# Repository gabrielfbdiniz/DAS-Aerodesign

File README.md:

# DAS V2 — Sistema de Aquisição de Dados de Voo
**Equipe de AeroDesign — Temporada 2025/2026**  
*Placa de Aviônica Integrada, Telemetria e Posicionamento GNSS RTK Centimétrico*

[-red.svg)](https://www.st.com)

---

## 1. Visão Geral do Projeto

O **DAS V2 (Data Acquisition System V2)** é a nova geração da aviônica de bordo da aeronave da equipe de AeroDesign. 

Projetada a partir do zero para superar as limitações térmicas e de estabilidade da versão anterior (V1), a placa unifica em um único PCB de 4 camadas:
* Processamento matemático de alto desempenho com FPU de ponto flutuante em hardware;
* Posicionamento geodésico centimétrico ($1\text{ cm} - 2\text{ cm}$) via RTK/PPK multibanda;
* Fusão de dados inerciais de 9 graus de liberdade (IMU);
* Telemetria do trem de força elétrico via barramento CAN ligado ao VESC;
* Armazenamento em alta velocidade em cartão MicroSD via SPI com DMA;
* Alimentação chaveada de alta eficiência suportando baterias LiPo 2S a 4S ($7.4\text{ V} - 16.8\text{ V}$) sem aquecimento.

---

## 2. Renders 3D da Placa (PCB 4 Camadas — 50 × 90 mm)

| Vista Superior (Top — `F.Cu`) | Vista Inferior (Bottom — `B.Cu`) |
| :---: | :---: |
|  |  |

---

## 3. Especificações Técnicas

| Subsistema | Componente / Chip | Características Principais |
| :--- | :--- | :--- |
| **Dimensões / Stackup** | **PCB 4 Camadas** ($50 \times 90\text{ mm}$) | Empilhamento `F.Cu` / `In1.Cu` (GND) / `In2.Cu` (PWR) / `B.Cu`, 128 componentes (passivos 0603 *HandSolder*). |
| **Microcontrolador** | **STM32G431CBT6** (LQFP-48) | ARM Cortex-M4F @ 170 MHz com FPU, 128 kB Flash, 32 kB SRAM, FDCAN nativo, cristal HSE 16 MHz. |
| **GNSS RTK** | **u-blox ZED-F9P-02B** | Receptor multibanda L1/L2 (GPS, GLONASS, Galileo, BeiDou), RTK centimétrico e logs brutos para PPK. |
| **Linha RF GNSS** | Conector SMA Borda 50 $\Omega$ (`J8`) | Bias-T ativo onboard (`VCC_RF`), filtro choke 47 nH e diodo TVS de ultrabaixa capacitância **PESD5V0X1BA**. |
| **IMU (9-DOF)** | **Bosch BNO055** | Acelerômetro, Giroscópio e Magnetômetro com fusão em quatérnions via I2C1 (`0x28`). |
| **Barômetro** | **TE MS5611-01BA** | Sensor barométrico de alta resolução (24 bits) no barramento I2C1 (`0x77`). |
| **Multiplexador I2C** | **TI PCA9548APW** | Multiplexador I2C de 8 canais no barramento I2C3 (`0x70`), com 4 portas JST-PH dedicadas (`J4`, `J12`–`J14`) para Pitot e expansões. |
| **Telemetria VESC / CAN** | **SN65HVD230** + TVS **NUP2105L** | Transceptor CAN 3.3V com terminação split $120\,\Omega$ configurável (`JP1`/`JP2`) e dois conectores JST-PH (`J7` VESC e `J10` Expansão). |
| **Armazenamento** | Slot MicroSD (`J5`, Push-Push) | Interface SPI1 de alta velocidade com DMA (>1.5 MB/s de escrita sustentada), montado na face inferior. |
| **Telemetria RF & Pixhawk** | Conectores JST-PH 2.0 mm (`J6`, `J11`) | UART2 dedicada para rádio modem de longo alcance (`J6`) e UART3 para interface Pixhawk / MAVLink (`J11`). |
| **Interface USB** | Conector USB-C 16 Pinos (`J2`) | Proteção ESD dedicada **USBLC6-2SC6**, resistores CC de $5.1\text{ k}\Omega$ e proteção de sobretensão (`3.3 V`) para `V_USB` do GNSS. |
| **Alimentação** | **TPS563200** + **AP2112K-3.3** | Buck 5.0V @ 2A (eficiência $>90\%$) + LDO 3.3V de baixo ruído, entrada XT30 (`J1`) 7.4V–16.8V (LiPo 2S–4S) com proteção P-MOSFET. |

---

## 4. Arquitetura Estrutural do Repositório

O repositório adota estrutura de **monorepo** separando hardware (KiCad 10), firmware (`STM32G431CBT6`) e documentação:

```
DAS_V2/
├── .gitignore                          # Regras de exclusão de temporários, backups e builds
├── README.md                           # Documentação principal do projeto
├── docs/                               # Documentação Técnica Aprofundada
│   ├── images/                         # Renders 3D da PCB (Top, Bottom e Isométrico)
│   │   ├── das_v2_iso.png
│   │   ├── das_v2_top.png
│   │   └── das_v2_bottom.png
│   ├── GUIA_OPERACAO_RTK_PPK.md        # Guia Completo: Operação RTK, Base de Solo, NTRIP e PPK
│   ├── RELATORIO_AUDITORIA_ESQUEMATICO_DAS_V2.md
│   └── PLANO_DE_ACAO.md                # Diagnóstico forense da V1 e diretrizes do redesenho V2
├── hardware/                           # Projeto KiCad 10 (Esquemático, PCB e Bibliotecas)
│   ├── DAS_V2.kicad_pro                # Arquivo principal do projeto KiCad 10
│   ├── DAS_V2.kicad_sch                # Folha Raiz (Top-Level) com barramentos interfolhas
│   ├── 01_Power_Supply.kicad_sch       # Módulo 1: Entrada XT30, Proteção P-FET, Buck 5V e LDO 3.3V
│   ├── 02_MCU_Core.kicad_sch           # Módulo 2: STM32G431, USB-C, SWD, HSE 16MHz, Reset & Status
│   ├── 03_Sensors.kicad_sch            # Módulo 3: IMU BNO055, Barômetro MS5611 e Mux I2C3 PCA9548APW
│   ├── 04_GNSS_RTK.kicad_sch           # Módulo 4: u-blox ZED-F9P, Bias-T, Linha RF 50R e Porta RTCM
│   ├── 05_Storage_Telemetry.kicad_sch  # Módulo 5: MicroSD, CAN (VESC + Expansão), RF e Pixhawk
│   ├── DAS_V2.kicad_pcb                # Layout da Placa de Circuito Impresso (Stackup 4 camadas)
│   ├── fp-lib-table                    # Tabela de bibliotecas de footprints locais
│   ├── sym-lib-table                   # Tabela de bibliotecas de símbolos locais
│   └── DAS_V2.pretty/                  # Diretório de footprints customizados (Logo AeroDesign)
└── firmware/                           # Firmware embarcado STM32G431CBT6
    └── README.md                       # Mapeamento de periféricos e instruções de firmware
```

---

## 5. Documentação Técnica em Destaque

* 🛰️ **[Guia de Operação GNSS RTK & PPK](docs/GUIA_OPERACAO_RTK_PPK.md):**
  Explica o funcionamento do ZED-F9P, por que o receptor sozinho no avião não atinge precisão centimétrica sem base, como **reaproveitar uma segunda placa DAS V2 idêntica como Estação de Solo em tripé**, como usar a rede gratuita NTRIP/IBGE (RBMC) e o passo a passo de pós-processamento com o **RTKLIB** (PPK).
* 🔍 **[Relatório de Auditoria Elétrica do Esquemático](docs/RELATORIO_AUDITORIA_ESQUEMATICO_DAS_V2.md):**
  Auditoria pino a pino de todos os CIs, apontando as correções críticas de hardware (Zener do P-MOSFET, estabilidade do LDO com cerâmica, bootloader do STM32 vs. CAN RX e capacitância do TVS de RF).
* 📋 **[Plano de Ação e Diagnóstico da V1](docs/PLANO_DE_ACAO.md):**
  Histórico forense das falhas da versão anterior e justificativas de engenharia para cada escolha de arquitetura da V2.

---

## 6. Como Abrir e Compilar o Projeto

1. Certifique-se de ter o **KiCad 10.0** ou superior instalado.
2. Clone o repositório:
   ```bash
   git clone <URL_DO_REPOSITORIO>
   cd "DAS V2"
   ```
3. Abra o arquivo de projeto:
   * Abra o KiCad e selecione `hardware/DAS_V2.kicad_pro`.
   * Clique em `Esquemático (Eeschema)` para visualizar as folhas hierárquicas.
   * Clique em `Placa (Pcbnew)` para visualizar o layout 2D/3D.

---

## 7. Padronização Mecânica e Conectores

Todos os chicotes externos da aeronave foram padronizados para garantir segurança contra vibração, leveza e facilidade de manutenção em campo:

| Conector | Função | Pinos | Padrão |
| :--- | :--- | :---: | :--- |
| **J1** | Entrada de Bateria Principal | 2 | **XT30** Vertical (`AMASS XT30UPB-M`) |
| **J2** | Interface de Programação / Dados | 16 | **USB-C** 2.0 (UFP) |
| **J3** | Debug / Gravação Firmware | 5 | SWD Header 2.54 mm (3.3V, SWDIO, SWCLK, GND, NRST) |
| **J4, J12, J13, J14** | Expansão I2C Multiplexada (Pitot / Sensores) | 4 | **JST-PH 2.0 mm** Vertical (Canais `0..3` do `PCA9548APW`) |
| **J5** | Armazenamento Local | 8+ | Slot **MicroSD** Push-Push (`Hirose DM3AT`, face inferior) |
| **J6** | Telemetria RF de Longo Alcance | 4 | **JST-PH 2.0 mm** Vertical (5.0V, GND, TX, RX — `USART2`) |
| **J7** | Telemetria VESC do Motor | 4 | **JST-PH 2.0 mm** Vertical (NC, CAN_H, CAN_L, GND) |
| **J8** | Antena GNSS Multibanda | Coaxial | **SMA Fêmea** Borda (`Edge-Mount`) 50 $\Omega$ |
| **J9** | Entrada de Correção RTCM | 4 | **JST-PH 2.0 mm** Vertical (3.3V, TX, RX, GND — `UART2` ZED-F9P) |
| **J10** | Expansão Barramento CAN | 4 | **JST-PH 2.0 mm** Vertical (CAN_H, CAN_L, GND) |
| **J11** | Interface Pixhawk / MAVLink | 4 | **JST-PH 2.0 mm** Vertical (`USART3` TX, RX, GND) |

---
*Desenvolvido com excelência técnica pela Equipe AeroDesign.*

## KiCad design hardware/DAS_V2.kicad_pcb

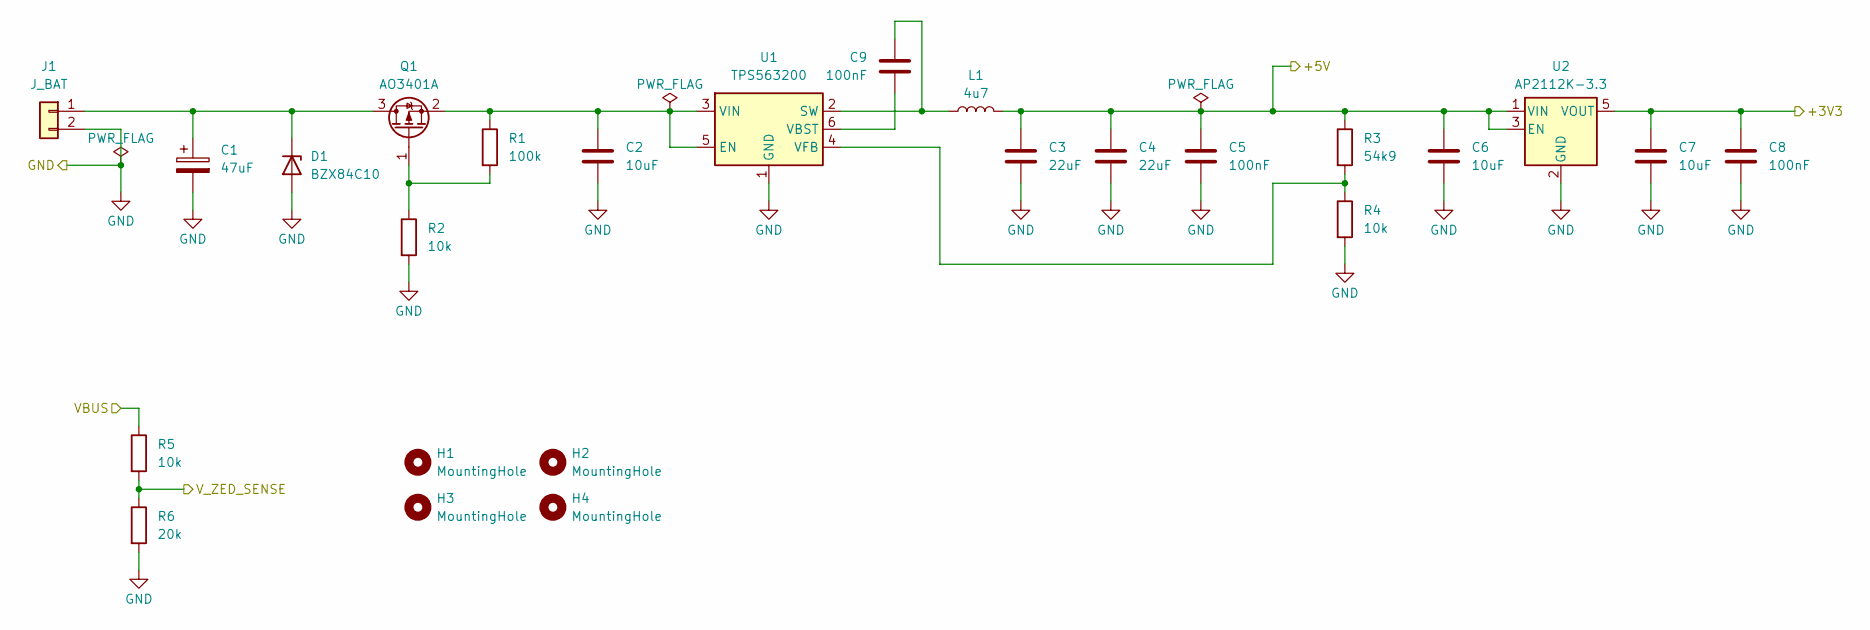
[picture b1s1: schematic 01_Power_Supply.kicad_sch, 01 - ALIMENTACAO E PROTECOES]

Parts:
C1: 47uF; CP_EIA-7343-31_Kemet-D_HandSolder
C2, C6, C7: 10uF; C_0805_2012Metric_Pad1.18x1.45mm_HandSolder
C3, C4: 22uF; C_1206_3216Metric_Pad1.33x1.80mm_HandSolder
C5, C8, C9: 100nF; C_0603_1608Metric_Pad1.08x0.95mm_HandSolder
D1: BZX84C10; SOT-23
H1, H2, H3, H4: MountingHole; MountingHole_3.2mm_M3
J1: J_BAT; AMASS_XT30UPB-M_1x02_P5.0mm_Vertical
L1: 4u7; L_APV_APH0630
Q1: AO3401A; SOT-23
R1: 100k; R_0603_1608Metric_Pad0.98x0.95mm_HandSolder
R2, R4, R5: 10k; R_0603_1608Metric_Pad0.98x0.95mm_HandSolder
R3: 54k9; R_0603_1608Metric_Pad0.98x0.95mm_HandSolder
R6: 20k; R_0603_1608Metric_Pad0.98x0.95mm_HandSolder
U1: TPS563200; SOT-23-6
U2: AP2112K-3.3; SOT-23-5

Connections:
/01_Alimentacao/+3V3: C7.1, C8.1, U2.5 (VOUT); also elsewhere on the board
/01_Alimentacao/+5V: C3.1, C4.1, C5.1, C6.1, L1.2, R3.1, U2.1 (VIN), U2.3 (EN); also elsewhere on the board
/01_Alimentacao/VBUS: R5.1; also elsewhere on the board
/01_Alimentacao/V_ZED_SENSE: R5.2, R6.1; also elsewhere on the board
GND: C1.2, C2.2, C3.2, C4.2, C5.2, C6.2, C7.2, C8.2, D1.1 (A), J1.2, R2.2, R4.2, R6.2, U1.1 (GND), U2.2 (GND); also elsewhere on the board
unnamed: C1.1, D1.3 (K), J1.1, Q1.3 (D)
unnamed: Q1.1 (G), R1.2, R2.1
unnamed: C2.1, Q1.2 (S), R1.1, U1.3 (VIN), U1.5 (EN)
unnamed: C9.1, L1.1, U1.2 (SW)
unnamed: C9.2, U1.6 (VBST)
unnamed: R3.2, R4.1, U1.4 (VFB)

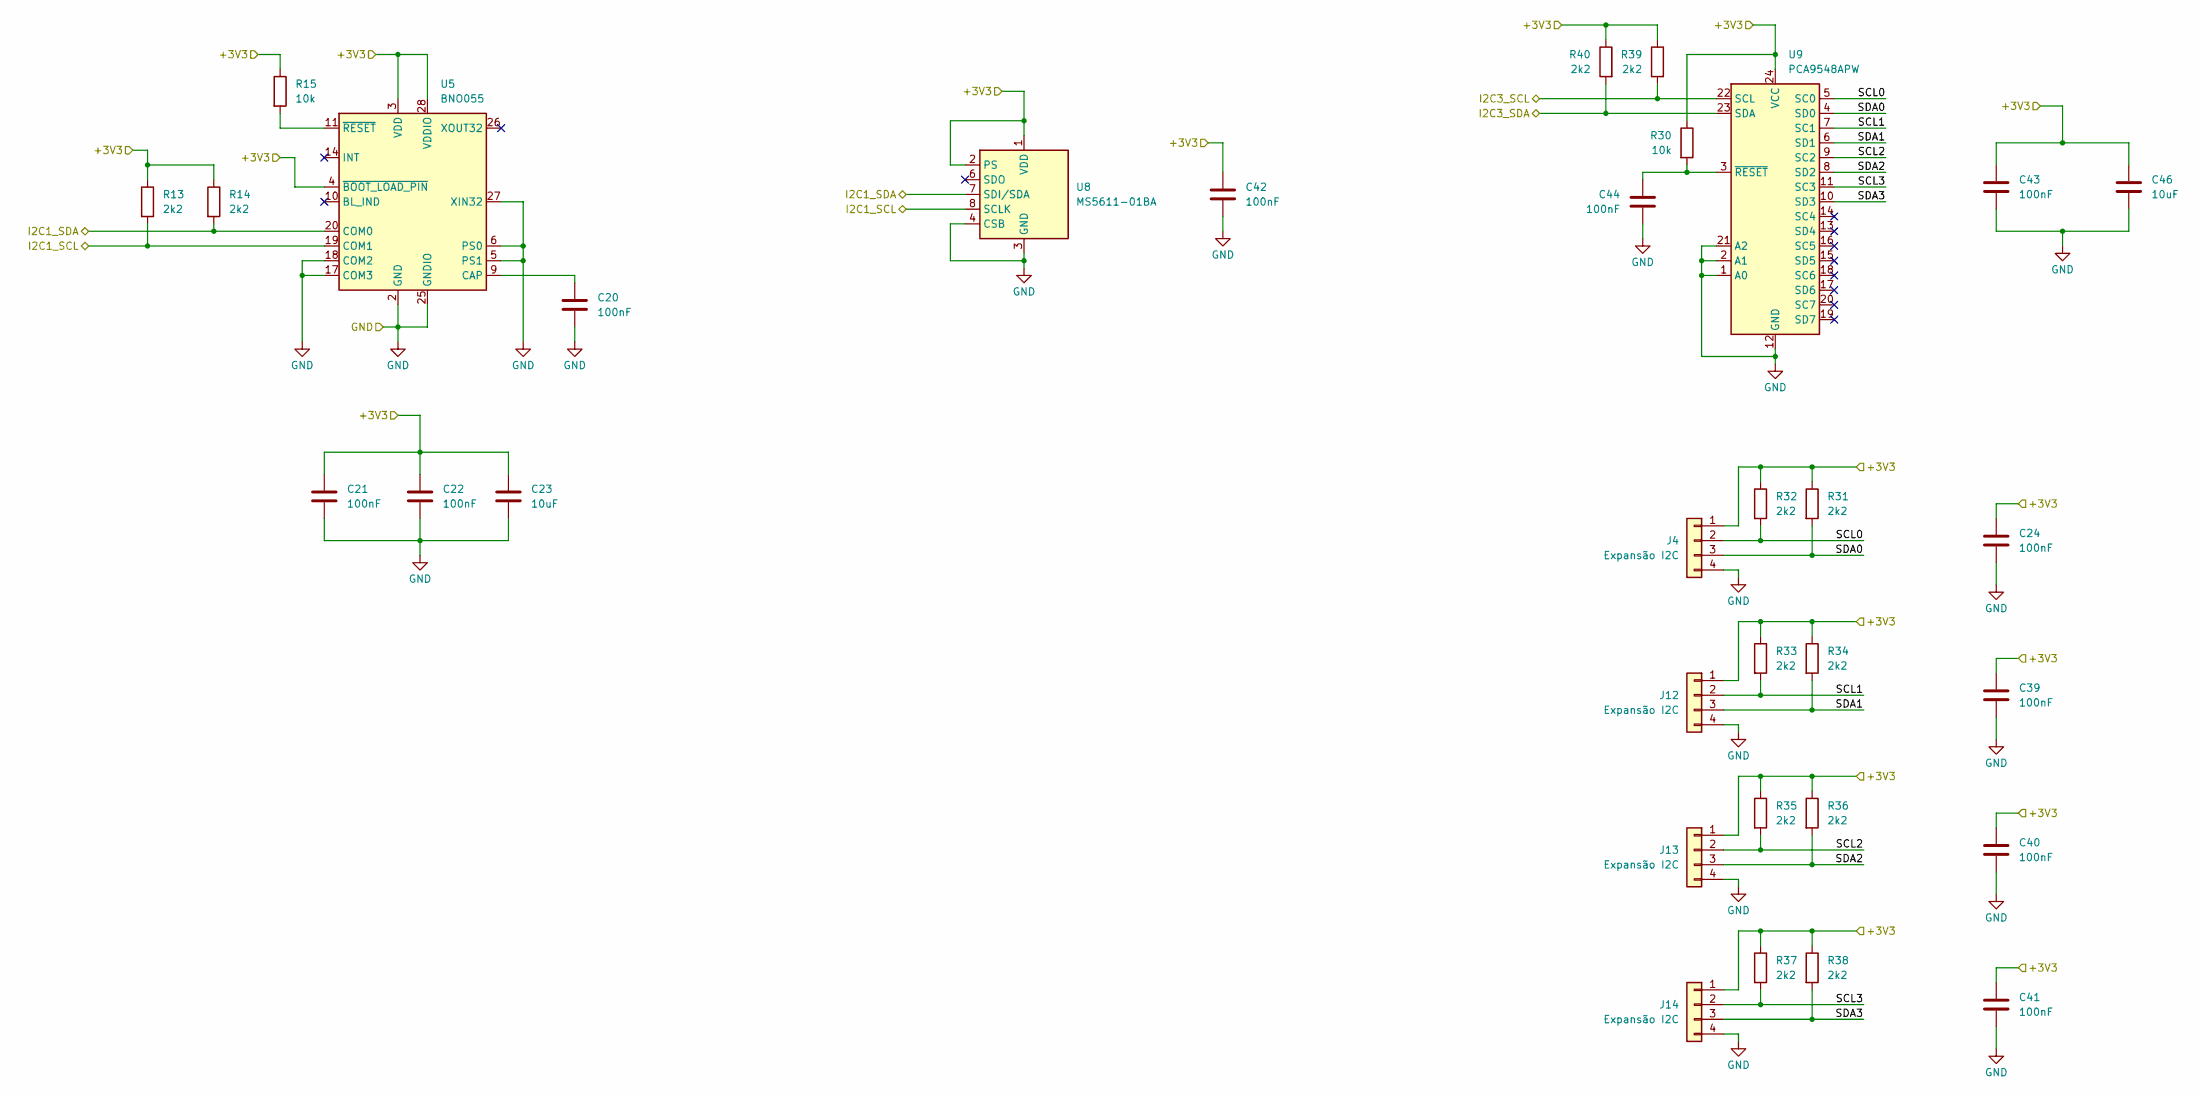
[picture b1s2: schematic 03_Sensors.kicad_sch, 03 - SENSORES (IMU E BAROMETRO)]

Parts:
C20, C21, C22, C24, C39, C40, C41, C42, C43, C44: 100nF; C_0603_1608Metric_Pad1.08x0.95mm_HandSolder
C23, C46: 10uF; C_0805_2012Metric_Pad1.18x1.45mm_HandSolder
J4, J12, J13, J14: Expansão I2C; JST_PH_B4B-PH-K_1x04_P2.00mm_Vertical
R13, R14, R31, R32, R33, R34, R35, R36, R37, R38, R39, R40: 2k2; R_0603_1608Metric_Pad0.98x0.95mm_HandSolder
R15, R30: 10k; R_0603_1608Metric_Pad0.98x0.95mm_HandSolder
U5: BNO055; LGA-28_5.2x3.8mm_P0.5mm
U8: MS5611-01BA; LGA-8_3x5mm_P1.25mm
U9: PCA9548APW; TSSOP-24_4.4x7.8mm_P0.65mm

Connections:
/01_Alimentacao/+3V3: C21.1, C22.1, C23.1, C24.1, C39.1, C40.1, C41.1, C42.1, C43.1, C46.1, J4.1, J12.1, J13.1, J14.1, R13.1, R14.1, R15.1, R30.1, R31.1, R32.1, R33.1, R34.1, R35.1, R36.1, R37.1, R38.1, R39.1, R40.1, U5.3 (VDD), U5.4 (~BOOT_LOAD_PIN), U5.28 (VDDIO), U8.1 (VDD), U8.2 (PS), U9.24 (VCC); also elsewhere on the board
/02_MCU_Core/I2C1_SCL: R13.2, U5.19 (COM1), U8.8 (SCLK); also elsewhere on the board
/02_MCU_Core/I2C1_SDA: R14.2, U5.20 (COM0), U8.7 (SDI/SDA); also elsewhere on the board
/02_MCU_Core/I2C3_SCL: R39.2, U9.22 (SCL); also elsewhere on the board
/02_MCU_Core/I2C3_SDA: R40.2, U9.23 (SDA); also elsewhere on the board
/03_Sensores/SCL0: J4.2, R32.2, U9.5 (SC0)
/03_Sensores/SCL1: J12.2, R33.2, U9.7 (SC1)
/03_Sensores/SCL2: J13.2, R35.2, U9.9 (SC2)
/03_Sensores/SCL3: J14.2, R37.2, U9.11 (SC3)
/03_Sensores/SDA0: J4.3, R31.2, U9.4 (SD0)
/03_Sensores/SDA1: J12.3, R34.2, U9.6 (SD1)
/03_Sensores/SDA2: J13.3, R36.2, U9.8 (SD2)
/03_Sensores/SDA3: J14.3, R38.2, U9.10 (SD3)
GND: C20.2, C21.2, C22.2, C23.2, C24.2, C39.2, C40.2, C41.2, C42.2, C43.2, C44.2, C46.2, J4.4, J12.4, J13.4, J14.4, U5.2 (GND), U5.5 (PS1), U5.6 (PS0), U5.17 (COM3), U5.18 (COM2), U5.25 (GNDIO), U5.27 (XIN32), U8.3 (GND), U8.4 (CSB), U8.5 (CSB), U9.1 (A0), U9.2 (A1), U9.12 (GND), U9.21 (A2); also elsewhere on the board
unnamed: C20.1, U5.9 (CAP)
unnamed: R15.2, U5.11 (~RESET)
unnamed: C44.1, R30.2, U9.3 (~RESET)

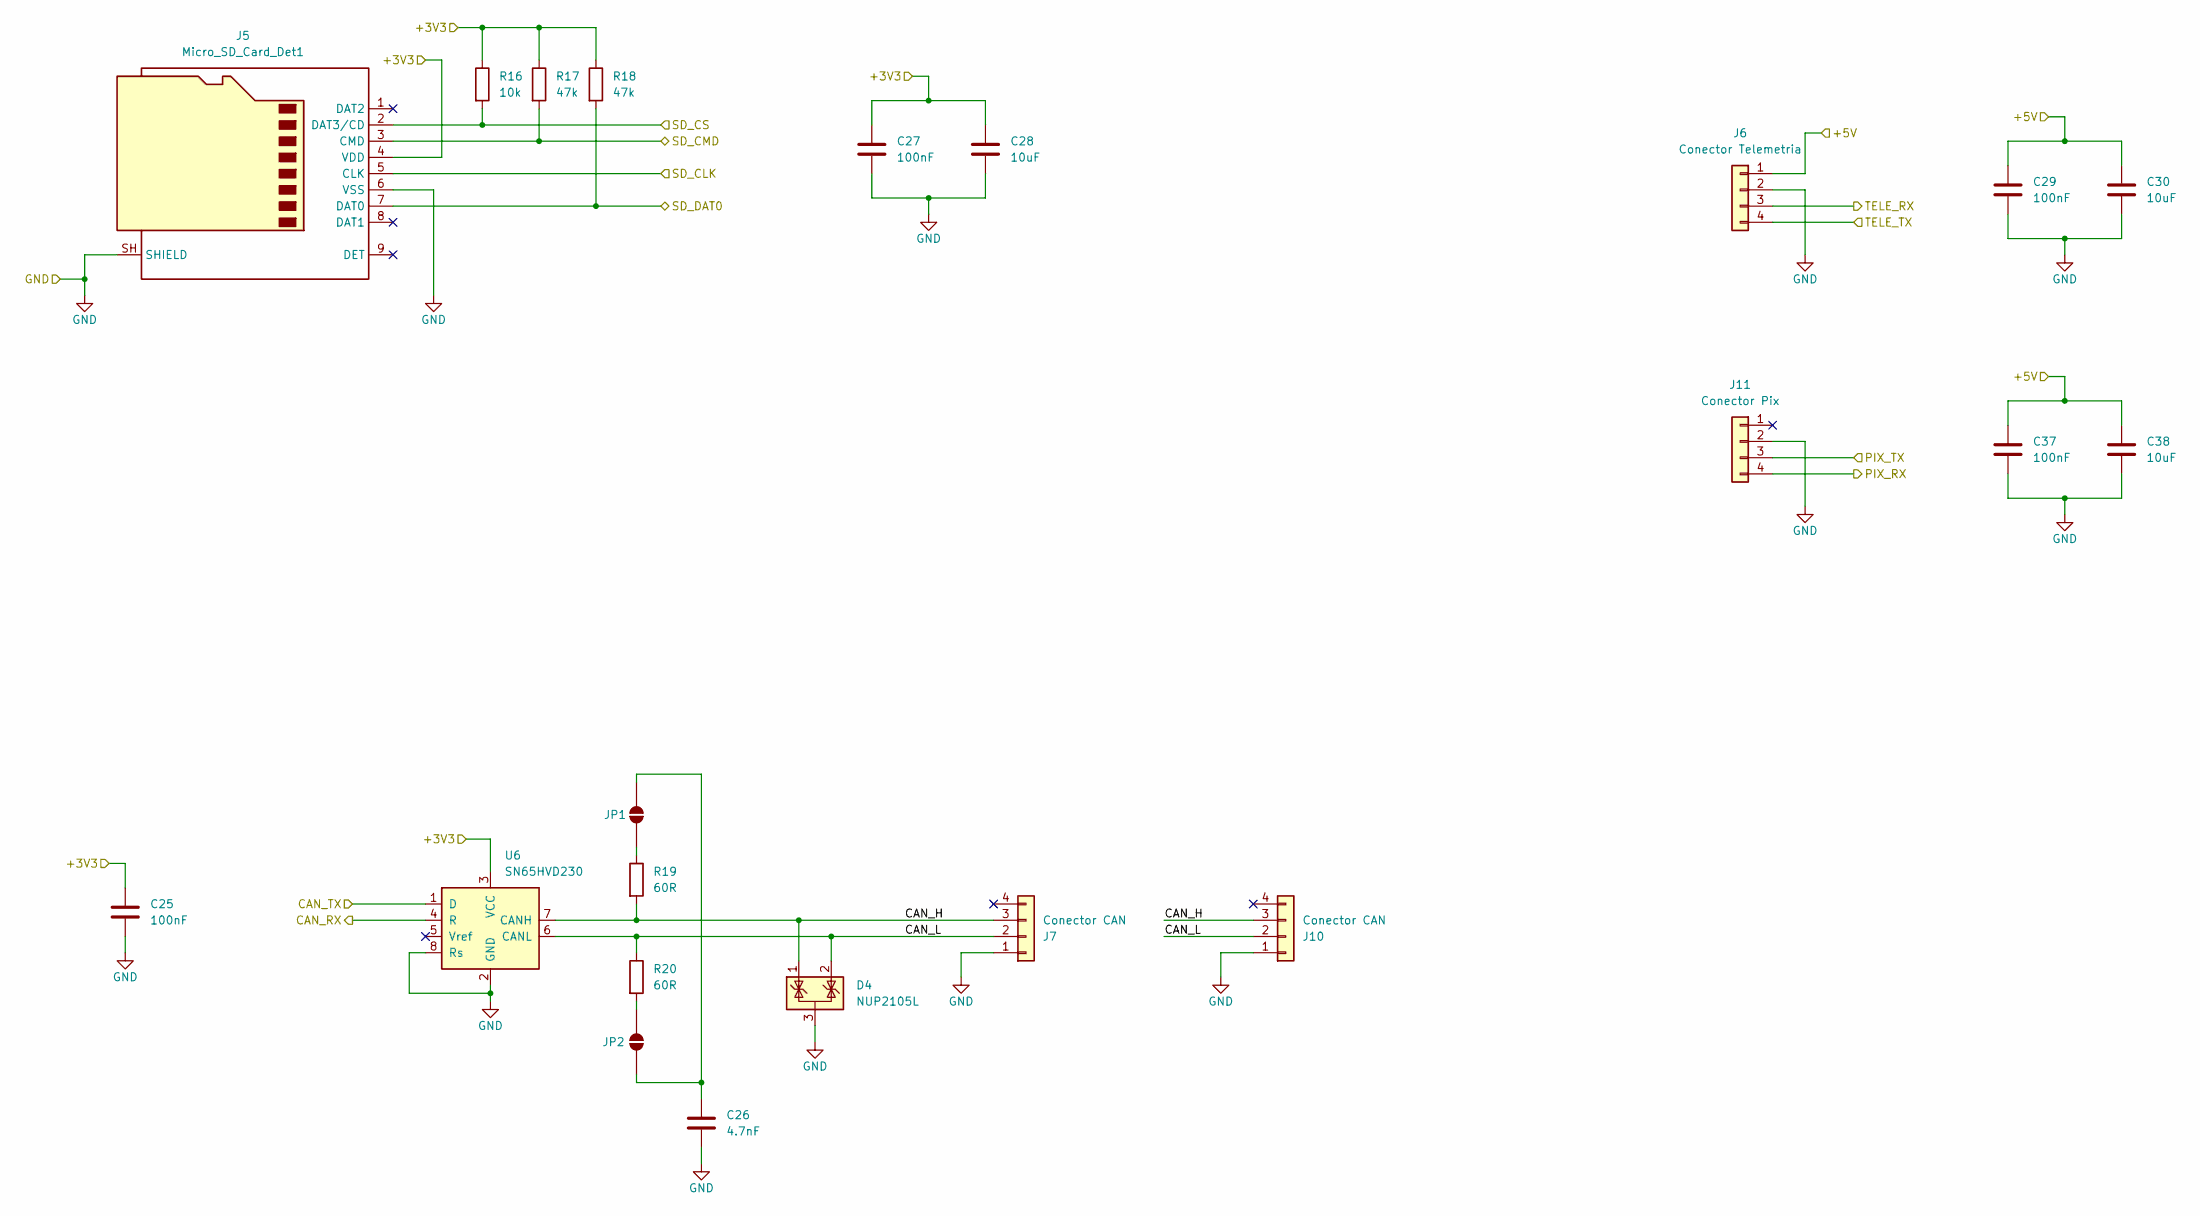
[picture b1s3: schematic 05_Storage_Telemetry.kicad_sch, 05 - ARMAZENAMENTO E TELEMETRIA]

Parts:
C25, C27, C29, C37: 100nF; C_0603_1608Metric_Pad1.08x0.95mm_HandSolder
C26: 4.7nF; C_0603_1608Metric_Pad1.08x0.95mm_HandSolder
C28, C30, C38: 10uF; C_0805_2012Metric_Pad1.18x1.45mm_HandSolder
D4: NUP2105L; SOT-23
J5: Micro_SD_Card_Det1; microSD_HC_Hirose_DM3AT-SF-PEJM5
J6: Conector Telemetria; JST_PH_B4B-PH-K_1x04_P2.00mm_Vertical
J7, J10: Conector CAN; JST_PH_B4B-PH-K_1x04_P2.00mm_Vertical
J11: Conector Pix; JST_PH_B4B-PH-K_1x04_P2.00mm_Vertical
JP1, JP2: SolderJumper_2_Open; SolderJumper-2_P1.3mm_Open_RoundedPad1.0x1.5mm
R16: 10k; R_0603_1608Metric_Pad0.98x0.95mm_HandSolder
R17, R18: 47k; R_0603_1608Metric_Pad0.98x0.95mm_HandSolder
R19, R20: 60R; R_0603_1608Metric_Pad0.98x0.95mm_HandSolder
U6: SN65HVD230; SOIC-8_3.9x4.9mm_P1.27mm

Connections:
/01_Alimentacao/+3V3: C25.1, C27.1, C28.1, J5.4 (VDD), R16.1, R17.1, R18.1, U6.3 (VCC); also elsewhere on the board
/01_Alimentacao/+5V: C29.1, C30.1, C37.1, C38.1, J6.1; also elsewhere on the board
/02_MCU_Core/CAN_RX: U6.4 (R); also elsewhere on the board
/02_MCU_Core/CAN_TX: U6.1 (D); also elsewhere on the board
/02_MCU_Core/PIX_RX: J11.4; also elsewhere on the board
/02_MCU_Core/PIX_TX: J11.3; also elsewhere on the board
/02_MCU_Core/SD_CLK: J5.5 (CLK); also elsewhere on the board
/02_MCU_Core/SD_CMD: J5.3 (CMD), R17.2; also elsewhere on the board
/02_MCU_Core/SD_CS: J5.2 (DAT3/CD), R16.2; also elsewhere on the board
/02_MCU_Core/SD_DAT0: J5.7 (DAT0), R18.2; also elsewhere on the board
/02_MCU_Core/TELE_RX: J6.3; also elsewhere on the board
/02_MCU_Core/TELE_TX: J6.4; also elsewhere on the board
/05_Armazenamento_Telemetria/CAN_H: D4.1 (K), J7.3, J10.3, R19.2, U6.7 (CANH)
/05_Armazenamento_Telemetria/CAN_L: D4.2 (K), J7.2, J10.2, R20.1, U6.6 (CANL)
GND: C25.2, C26.2, C27.2, C28.2, C29.2, C30.2, C37.2, C38.2, D4.3 (A), J5.6 (VSS), J5.SH (SHIELD), J6.2, J7.1, J10.1, J11.2, U6.2 (GND), U6.8 (Rs); also elsewhere on the board
unnamed: JP1.1 (A), R19.1
unnamed: C26.1, JP1.2 (B), JP2.1 (A)
unnamed: JP2.2 (B), R20.2

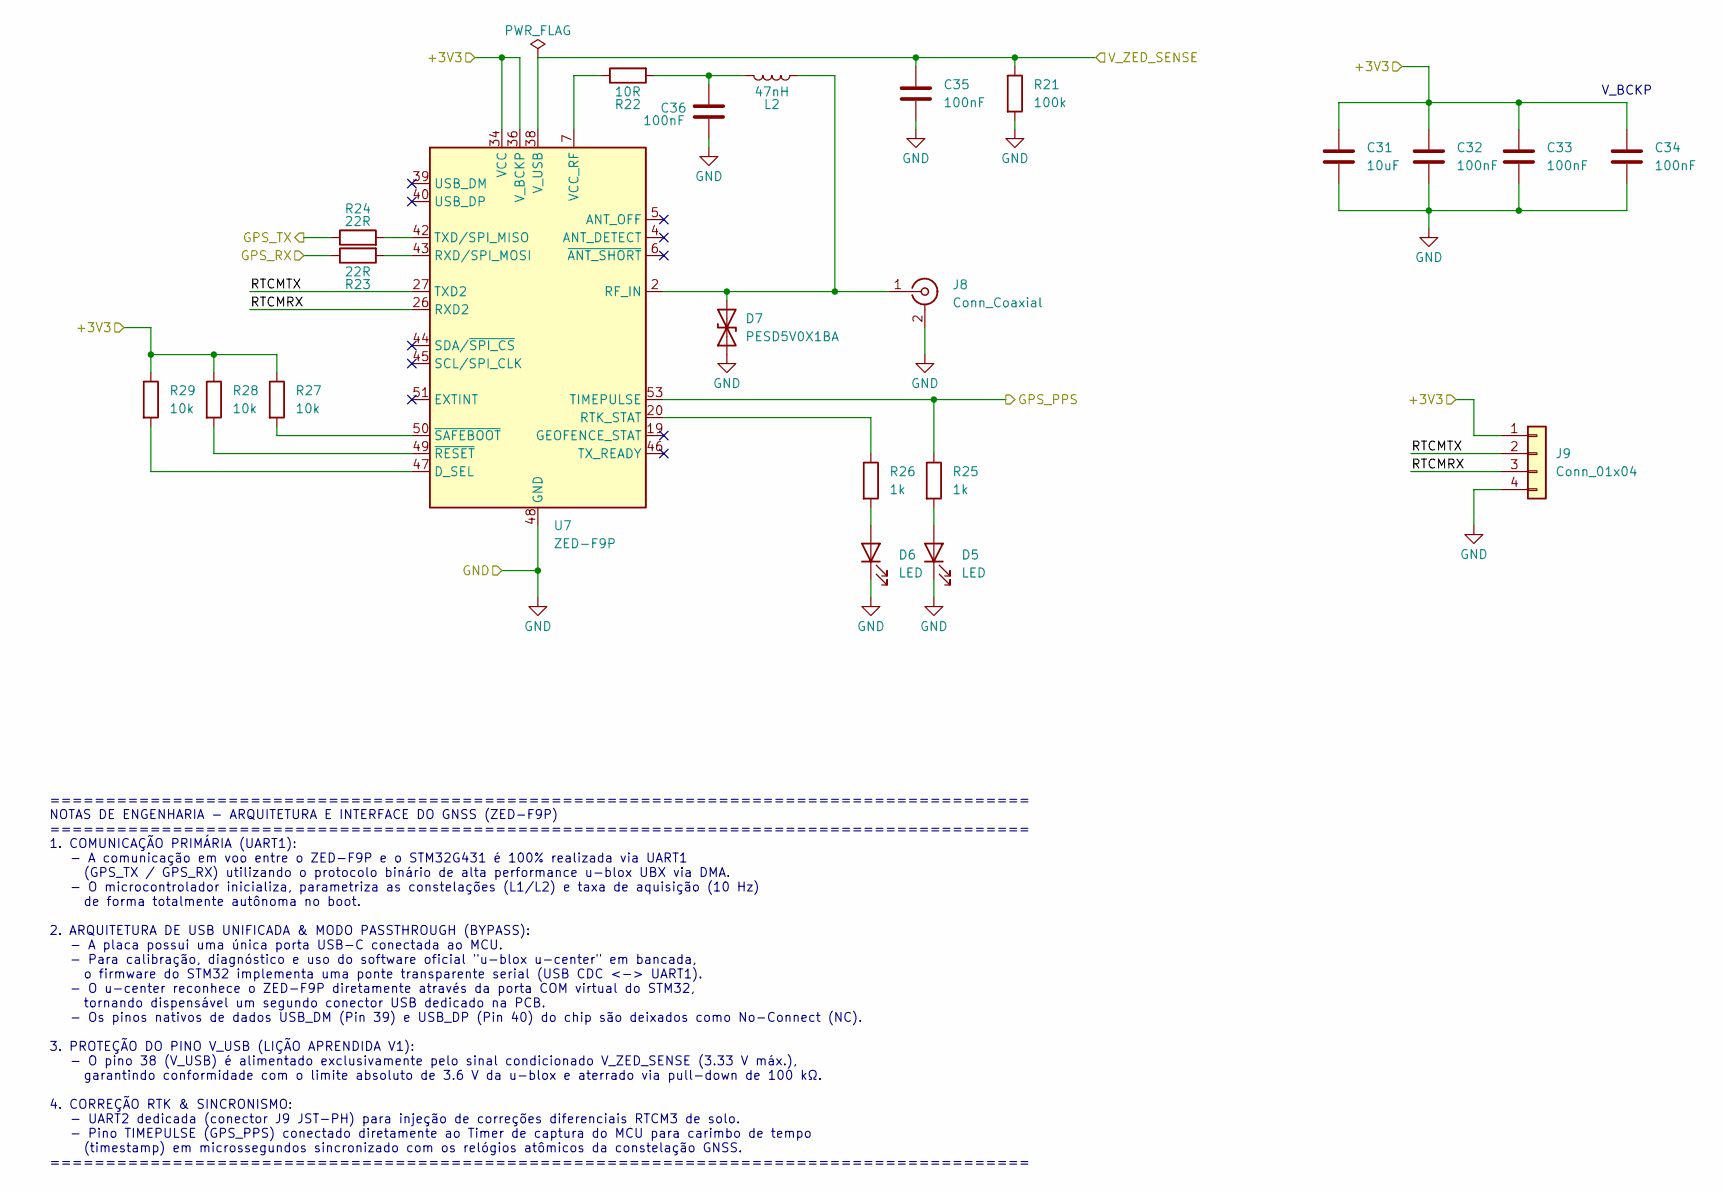
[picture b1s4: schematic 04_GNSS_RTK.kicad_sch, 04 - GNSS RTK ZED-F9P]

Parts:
C31: 10uF; C_0805_2012Metric_Pad1.18x1.45mm_HandSolder
C32, C33, C34, C35, C36: 100nF; C_0603_1608Metric_Pad1.08x0.95mm_HandSolder
D5, D6: LED; LED_0603_1608Metric_Pad1.05x0.95mm_HandSolder
D7: PESD5V0X1BA; D_SOD-323_HandSoldering
J8: Conn_Coaxial; SMA_Amphenol_132289_EdgeMount
J9: Conn_01x04; JST_PH_B4B-PH-K_1x04_P2.00mm_Vertical
L2: 47nH; L_0603_1608Metric_Pad1.05x0.95mm_HandSolder
R21: 100k; R_0603_1608Metric_Pad0.98x0.95mm_HandSolder
R22: 10R; R_0603_1608Metric_Pad0.98x0.95mm_HandSolder
R23, R24: 22R; R_0603_1608Metric_Pad0.98x0.95mm_HandSolder
R25, R26: 1k; R_0603_1608Metric_Pad0.98x0.95mm_HandSolder
R27, R28, R29: 10k; R_0603_1608Metric_Pad0.98x0.95mm_HandSolder
U7: ZED-F9P; ublox_ZED

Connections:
/01_Alimentacao/+3V3: C31.1, C32.1, C33.1, C34.1, J9.1, R27.1, R28.1, R29.1, U7.33 (VCC), U7.34 (VCC), U7.36 (V_BCKP); also elsewhere on the board
/01_Alimentacao/V_ZED_SENSE: C35.1, R21.1, U7.38 (V_USB); also elsewhere on the board
/02_MCU_Core/GPS_PPS: R25.1, U7.53 (TIMEPULSE); also elsewhere on the board
/02_MCU_Core/GPS_RX: R23.1; also elsewhere on the board
/02_MCU_Core/GPS_TX: R24.1; also elsewhere on the board
/04_GNSS_RTK/RTCMRX: J9.3, U7.26 (RXD2)
/04_GNSS_RTK/RTCMTX: J9.2, U7.27 (TXD2)
GND: C31.2, C32.2, C33.2, C34.2, C35.2, C36.2, D5.1 (K), D6.1 (K), D7.1 (A1), J8.2 (Ext), J9.4, R21.2, U7.1 (GND), U7.3 (GND), U7.12 (GND), U7.14 (GND), U7.32 (GND), U7.37 (GND), U7.41 (GND), U7.48 (GND), U7.55 (GND); also elsewhere on the board
unnamed: C36.1, L2.1, R22.2
unnamed: D5.2 (A), R25.2
unnamed: D6.2 (A), R26.2
unnamed: D7.2 (A2), J8.1 (In), L2.2, U7.2 (RF_IN)
unnamed: R29.2, U7.47 (D_SEL)
unnamed: R26.1, U7.20 (RTK_STAT)
unnamed: R23.2, U7.43 (RXD/SPI_MOSI)
unnamed: R24.2, U7.42 (TXD/SPI_MISO)
unnamed: R22.1, U7.7 (VCC_RF)
unnamed: R28.2, U7.49 (~RESET)
unnamed: R27.2, U7.50 (~SAFEBOOT)

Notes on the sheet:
V_BCKP
======================================================================================== NOTAS DE ENGENHARIA - ARQUITETURA E INTERFACE DO GNSS (ZED-F9P) ======================================================================================== 1. COMUNICAÇÃO PRIMÁRIA (UART1): - A comunicação em voo e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

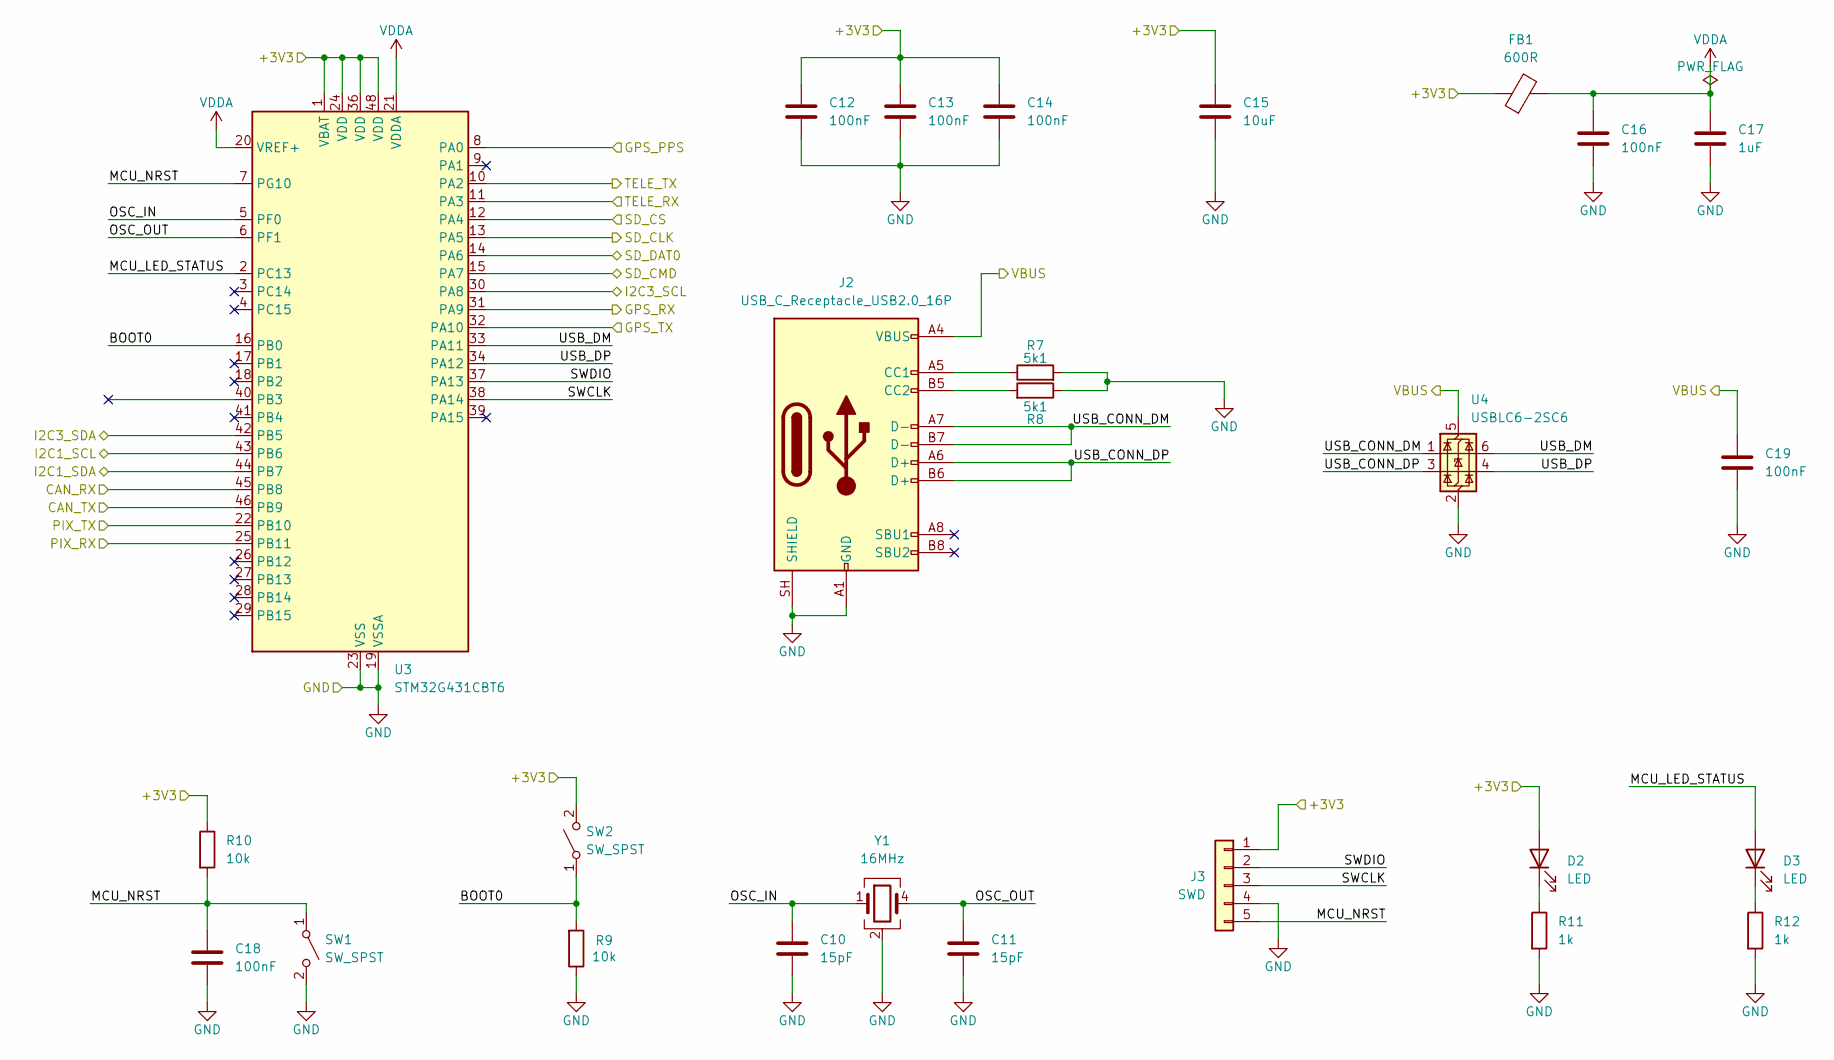
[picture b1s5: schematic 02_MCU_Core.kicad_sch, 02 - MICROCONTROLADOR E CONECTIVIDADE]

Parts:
C10, C11: 15pF; C_0603_1608Metric_Pad1.08x0.95mm_HandSolder
C12, C13, C14, C16, C18, C19: 100nF; C_0603_1608Metric_Pad1.08x0.95mm_HandSolder
C15: 10uF; C_0805_2012Metric_Pad1.18x1.45mm_HandSolder
C17: 1uF; C_0603_1608Metric_Pad1.08x0.95mm_HandSolder
D2, D3: LED; LED_0603_1608Metric_Pad1.05x0.95mm_HandSolder
FB1: 600R; L_0603_1608Metric_Pad1.05x0.95mm_HandSolder
J2: USB_C_Receptacle_USB2.0_16P; USB_C_Receptacle_GCT_USB4105-xx-A_16P_TopMnt_Horizontal
J3: SWD; PinHeader_1x05_P2.54mm_Vertical
R7, R8: 5k1; R_0603_1608Metric_Pad0.98x0.95mm_HandSolder
R9, R10: 10k; R_0603_1608Metric_Pad0.98x0.95mm_HandSolder
R11, R12: 1k; R_0603_1608Metric_Pad0.98x0.95mm_HandSolder
SW1, SW2: SW_SPST; SW_SPST_PTS645Sx43SMTR92
U3: STM32G431CBT6; LQFP-48_7x7mm_P0.5mm
U4: USBLC6-2SC6; SOT-23-6
Y1: 16MHz; Crystal_SMD_3225-4Pin_3.2x2.5mm_HandSoldering

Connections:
/01_Alimentacao/+3V3: C12.1, C13.1, C14.1, C15.1, D2.2 (A), FB1.1, J3.1, R10.1, SW2.2 (B), U3.1 (VBAT), U3.24 (VDD), U3.36 (VDD), U3.48 (VDD); also elsewhere on the board
/01_Alimentacao/VBUS: C19.1, J2.A4 (VBUS), J2.A9 (VBUS), J2.B4 (VBUS), J2.B9 (VBUS), U4.5 (VBUS); also elsewhere on the board
/02_MCU_Core/BOOT0: R9.2, SW2.1 (A), U3.16 (PB0)
/02_MCU_Core/CAN_RX: U3.45 (PB8); also elsewhere on the board
/02_MCU_Core/CAN_TX: U3.46 (PB9); also elsewhere on the board
/02_MCU_Core/GPS_PPS: U3.8 (PA0); also elsewhere on the board
/02_MCU_Core/GPS_RX: U3.31 (PA9); also elsewhere on the board
/02_MCU_Core/GPS_TX: U3.32 (PA10); also elsewhere on the board
/02_MCU_Core/I2C1_SCL: U3.43 (PB6); also elsewhere on the board
/02_MCU_Core/I2C1_SDA: U3.44 (PB7); also elsewhere on the board
/02_MCU_Core/I2C3_SCL: U3.30 (PA8); also elsewhere on the board
/02_MCU_Core/I2C3_SDA: U3.42 (PB5); also elsewhere on the board
/02_MCU_Core/MCU_LED_STATUS: D3.2 (A), U3.2 (PC13)
/02_MCU_Core/MCU_NRST: C18.1, J3.5, R10.2, SW1.1 (A), U3.7 (PG10)
/02_MCU_Core/OSC_IN: C10.1, U3.5 (PF0), Y1.1
/02_MCU_Core/OSC_OUT: C11.1, U3.6 (PF1), Y1.4
/02_MCU_Core/PIX_RX: U3.25 (PB11); also elsewhere on the board
/02_MCU_Core/PIX_TX: U3.22 (PB10); also elsewhere on the board
/02_MCU_Core/SD_CLK: U3.13 (PA5); also elsewhere on the board
/02_MCU_Core/SD_CMD: U3.15 (PA7); also elsewhere on the board
/02_MCU_Core/SD_CS: U3.12 (PA4); also elsewhere on the board
/02_MCU_Core/SD_DAT0: U3.14 (PA6); also elsewhere on the board
/02_MCU_Core/SWCLK: J3.3, U3.38 (PA14)
/02_MCU_Core/SWDIO: J3.2, U3.37 (PA13)
/02_MCU_Core/TELE_RX: U3.11 (PA3); also elsewhere on the board
/02_MCU_Core/TELE_TX: U3.10 (PA2); also elsewhere on the board
/02_MCU_Core/USB_CONN_DM: J2.A7 (D-), J2.B7 (D-), U4.1 (I/O1)
/02_MCU_Core/USB_CONN_DP: J2.A6 (D+), J2.B6 (D+), U4.3 (I/O2)
/02_MCU_Core/USB_DM: U3.33 (PA11), U4.6 (I/O1)
/02_MCU_Core/USB_DP: U3.34 (PA12), U4.4 (I/O2)
GND: C10.2, C11.2, C12.2, C13.2, C14.2, C15.2, C16.2, C17.2, C18.2, C19.2, J2.A1 (GND), J2.A12 (GND), J2.B1 (GND), J2.B12 (GND), J2.SH (SHIELD), J3.4, R7.2, R8.1, R9.1, R11.2, R12.2, SW1.2 (B), U3.19 (VSSA), U3.23 (VSS), U3.35 (VSS), U3.47 (VSS), U4.2 (GND), Y1.2 (G), Y1.3 (G); also elsewhere on the board
unnamed: D2.1 (K), R11.1
unnamed: D3.1 (K), R12.1
unnamed: J2.A5 (CC1), R7.1
unnamed: J2.B5 (CC2), R8.2
VDDA: C16.1, C17.1, FB1.2, U3.20 (VREF+), U3.21 (VDDA)

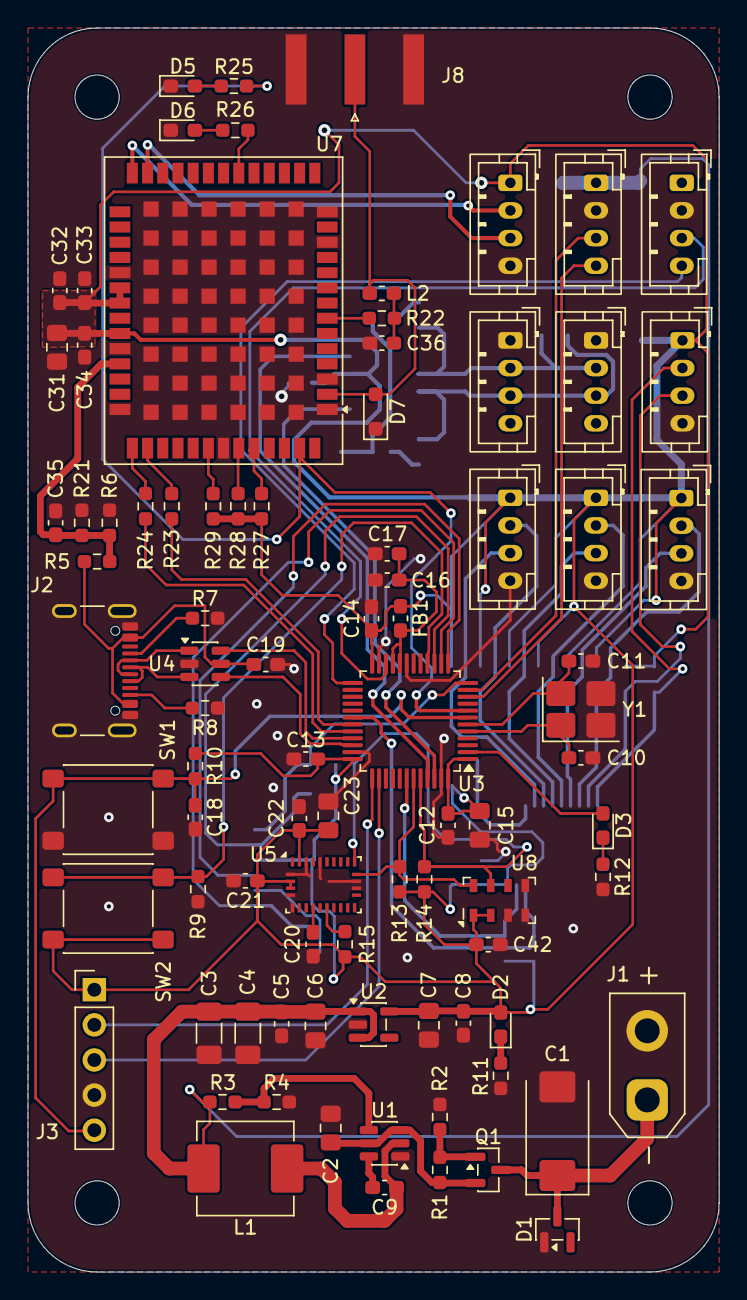
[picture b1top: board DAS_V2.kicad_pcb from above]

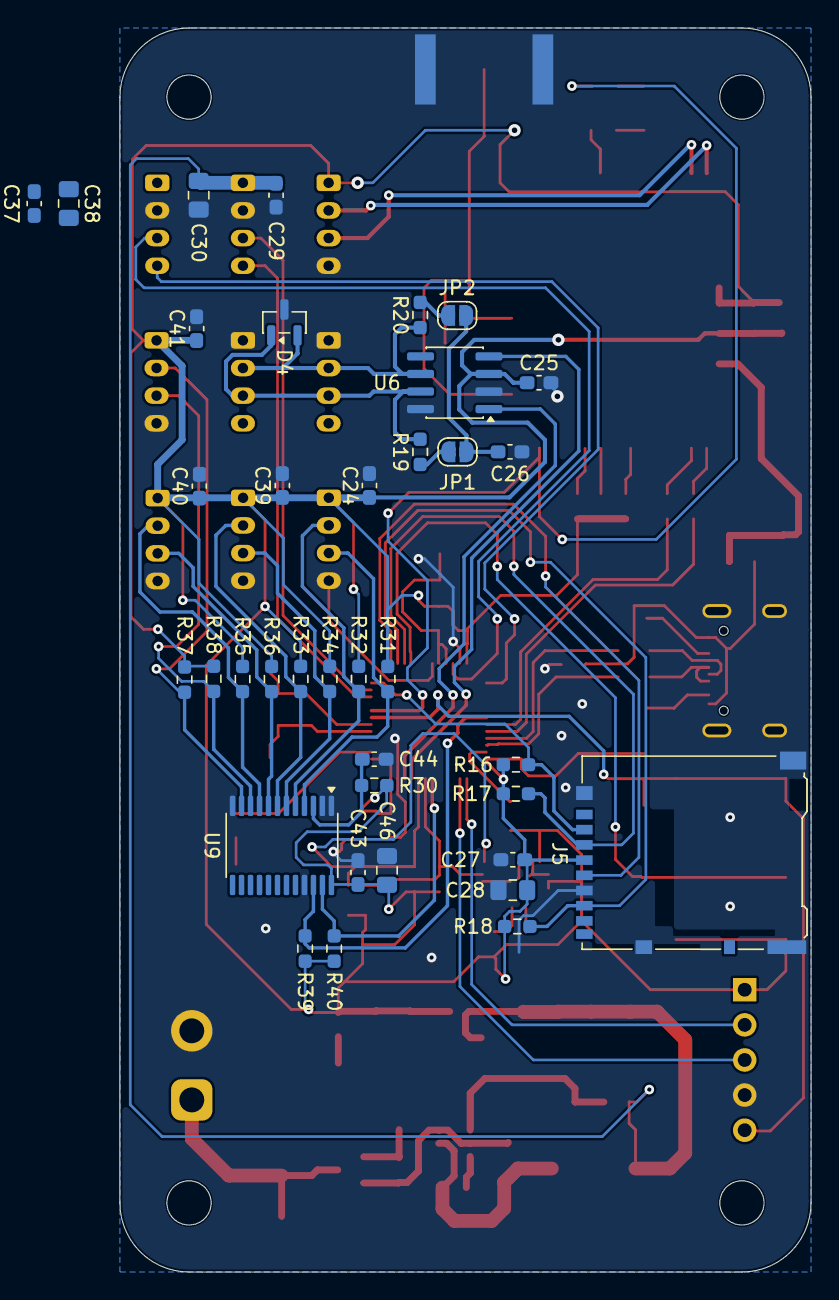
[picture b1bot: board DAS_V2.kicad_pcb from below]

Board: 4 copper layers, 50.0 x 90.0 mm, 128 parts (37 on the bottom side), 73 nets.
